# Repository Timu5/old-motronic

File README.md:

# old-motronic
This repo contains anything usable for reverse engineering old 8051 based motronic ecu like tools to dump eeprom, epprom adapters and docs.

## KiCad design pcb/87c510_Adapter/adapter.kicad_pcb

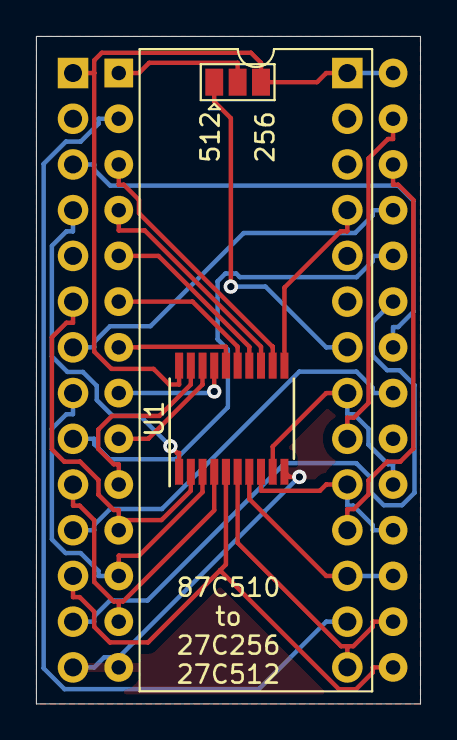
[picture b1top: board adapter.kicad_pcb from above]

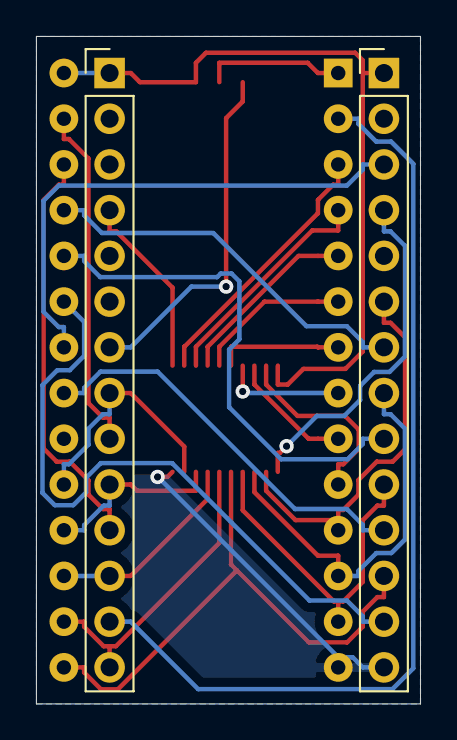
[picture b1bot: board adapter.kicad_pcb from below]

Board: 2 copper layers, 21.3 x 37.1 mm, 5 parts (2 on the bottom side), 30 nets.

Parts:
J1, J2: Conn_01x14; Pin_Header_Straight_1x14_Pitch2.54mm
JP1: 256/512; SolderJumper-3_P1.3mm_Open_Pad1.0x1.5mm
U1: 74LS573; TSSOP-20_4.4x6.5mm_Pitch0.65mm
U2: 27C512; DIP-28_W15.24mm

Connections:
+5V: J1.1, J2.1, JP1.3, U1.20, U2.28
A0: U1.19, U2.10
A1: U1.18, U2.9
A2: U1.17, U2.8
A3: U1.16, U2.7
A4: U1.15, U2.6
A5: U1.14, U2.5
A6: U1.13, U2.4
A7: U1.12, U2.3
A8: J1.7, U2.25
A9: J1.9, U2.24
A10: J1.11, U2.21
A11: J1.13, U2.23
A12: J2.13, U2.2
A13: J2.11, U2.26
A14: J2.9, U2.27
A15: J2.7, JP1.1
AD0: J1.6, U1.2, U2.11
AD1: J1.8, U1.3, U2.12
AD2: J1.10, U1.4, U2.13
AD3: J1.12, U1.5, U2.15
AD4: J2.14, U1.6, U2.16
AD5: J2.12, U1.7, U2.17
AD6: J2.10, U1.8, U2.18
AD7: J2.8, U1.9, U2.19
ALE: J2.4, U1.11
EN: J1.4, U1.1
GND: J1.14, U1.10, U2.14
unnamed: JP1.2, U2.1
OE: J1.3, U2.22

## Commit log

2019-09-11 Add internal memeory dumper
2019-09-12 Add start and end pulse
2019-09-13 Add serial disabling to dump_internal
2019-09-19 Add arduino 87c510 reader code
2019-09-21 Add arduino 27c256 reader code
2019-09-28 Add 87c510 datasheet
2019-09-28 Add 87c510 to 27c512 adapter schematic
2019-10-01 Update schematic
2019-10-01 Add pcb layout
